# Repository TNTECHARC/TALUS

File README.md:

# TALUS GEN II
New repository for 2nd get TALUS (Raspberry Pi base).

## Centralized cloud for code, hardware, and cad models.

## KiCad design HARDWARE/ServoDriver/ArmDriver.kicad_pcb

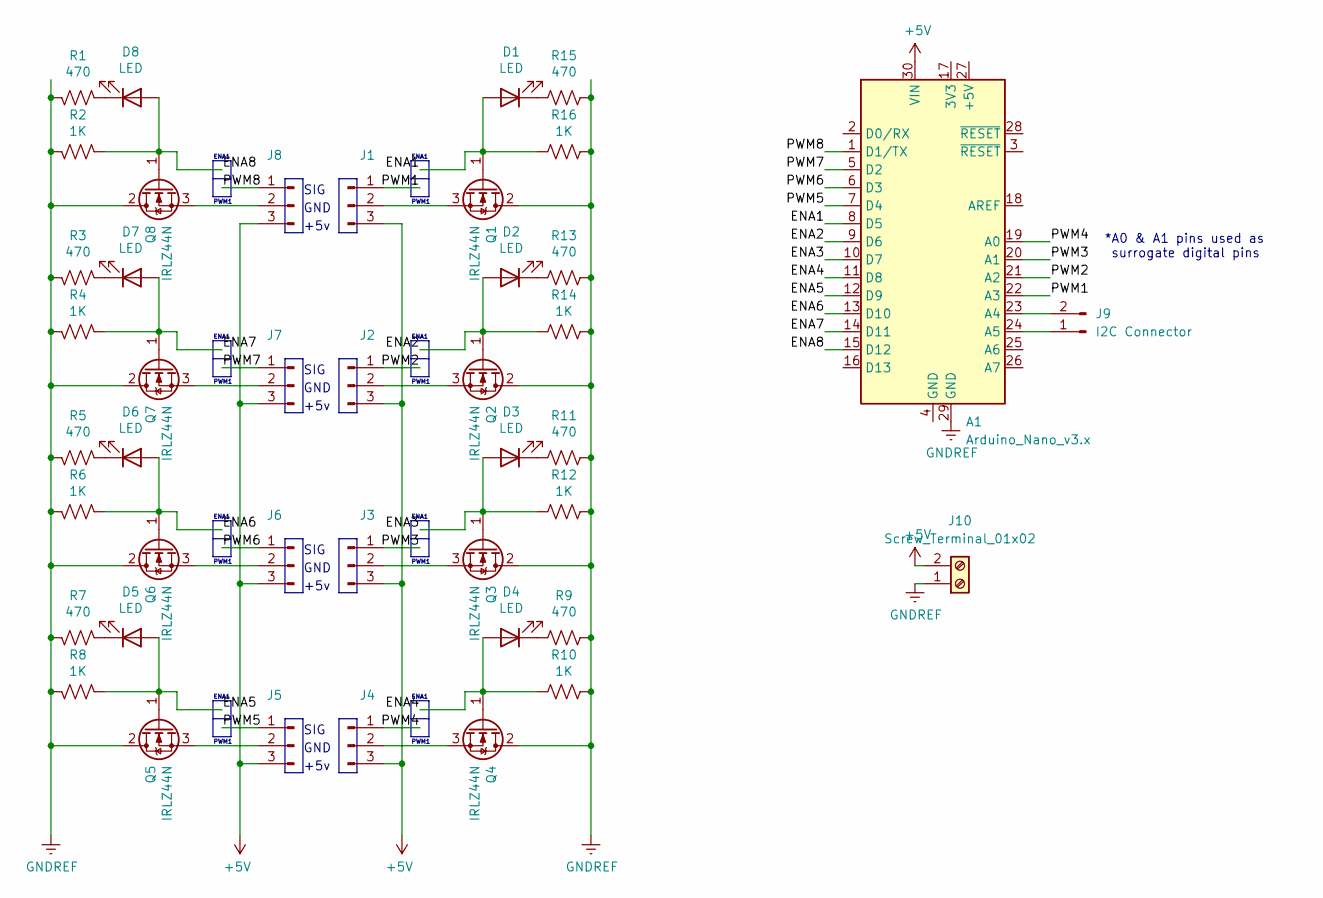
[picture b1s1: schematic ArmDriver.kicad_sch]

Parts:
A1: Arduino_Nano_v3.x; Arduino_Nano
D1, D2, D3, D4, D5, D6, D7, D8: LED; LED_D3.0mm
J1, J2, J3, J4, J5, J6, J7, J8: Conn_01x03_Male; PinHeader_1x03_P2.54mm_Vertical
J9: I2C Connector; PinHeader_1x02_P2.54mm_Vertical
J10: Screw_Terminal_01x02; TerminalBlock_Altech_AK300-2_P5.00mm
Q1, Q2, Q3, Q4, Q5, Q6, Q7, Q8: IRLZ44N; TO-218-3_Vertical
R1, R3, R5, R7, R9, R11, R13, R15: 470; R_Axial_DIN0204_L3.6mm_D1.6mm_P2.54mm_Vertical
R2, R4, R6, R8, R10, R12, R14, R16: 1K; R_Axial_DIN0204_L3.6mm_D1.6mm_P2.54mm_Vertical

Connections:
+5V: A1.30 (VIN), J1.3, J2.3, J3.3, J4.3, J5.3, J6.3, J7.3, J8.3, J10.2
/ENA1: A1.8 (D5), D1.2 (A), Q1.1 (G), R16.2
/ENA2: A1.9 (D6), D2.2 (A), Q2.1 (G), R14.2
/ENA3: A1.10 (D7), D3.2 (A), Q3.1 (G), R12.2
/ENA4: A1.11 (D8), D4.2 (A), Q4.1 (G), R10.2
/ENA5: A1.12 (D9), D5.2 (A), Q5.1 (G), R8.2
/ENA6: A1.13 (D10), D6.2 (A), Q6.1 (G), R6.2
/ENA7: A1.14 (D11), D7.2 (A), Q7.1 (G), R4.2
/ENA8: A1.15 (D12), D8.2 (A), Q8.1 (G), R2.2
/PWM1: A1.22 (A3), J1.1
/PWM2: A1.21 (A2), J2.1
/PWM3: A1.20 (A1), J3.1
/PWM4: A1.19 (A0), J4.1
/PWM5: A1.7 (D4), J5.1
/PWM6: A1.6 (D3), J6.1
/PWM7: A1.5 (D2), J7.1
/PWM8: A1.1 (D1/TX), J8.1
GNDREF: A1.29 (GND), J10.1, Q1.2 (D), Q2.2 (D), Q3.2 (D), Q4.2 (D), Q5.2 (D), Q6.2 (D), Q7.2 (D), Q8.2 (D), R1.1, R2.1, R3.1, R4.1, R5.1, R6.1, R7.1, R8.1, R9.1, R10.1, R11.1, R12.1, R13.1, R14.1, R15.1, R16.1; also elsewhere on the board
unnamed: A1.23 (A4), J9.2
unnamed: A1.24 (A5), J9.1
unnamed: D1.1 (K), R15.2
unnamed: D2.1 (K), R13.2
unnamed: D3.1 (K), R11.2
unnamed: D4.1 (K), R9.2
unnamed: D5.1 (K), R7.2
unnamed: D6.1 (K), R5.2
unnamed: D7.1 (K), R3.2
unnamed: D8.1 (K), R1.2
unnamed: J1.2, Q1.3 (S)
unnamed: J2.2, Q2.3 (S)
unnamed: J3.2, Q3.3 (S)
unnamed: J4.2, Q4.3 (S)
unnamed: J5.2, Q5.3 (S)
unnamed: J6.2, Q6.3 (S)
unnamed: J7.2, Q7.3 (S)
unnamed: J8.2, Q8.3 (S)
unnamed 36: A1.25 (A6); also elsewhere on the board

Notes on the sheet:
PWM1
SIG
ENA1
+5v
*A0 & A1 pins used as surrogate digital pins
GND

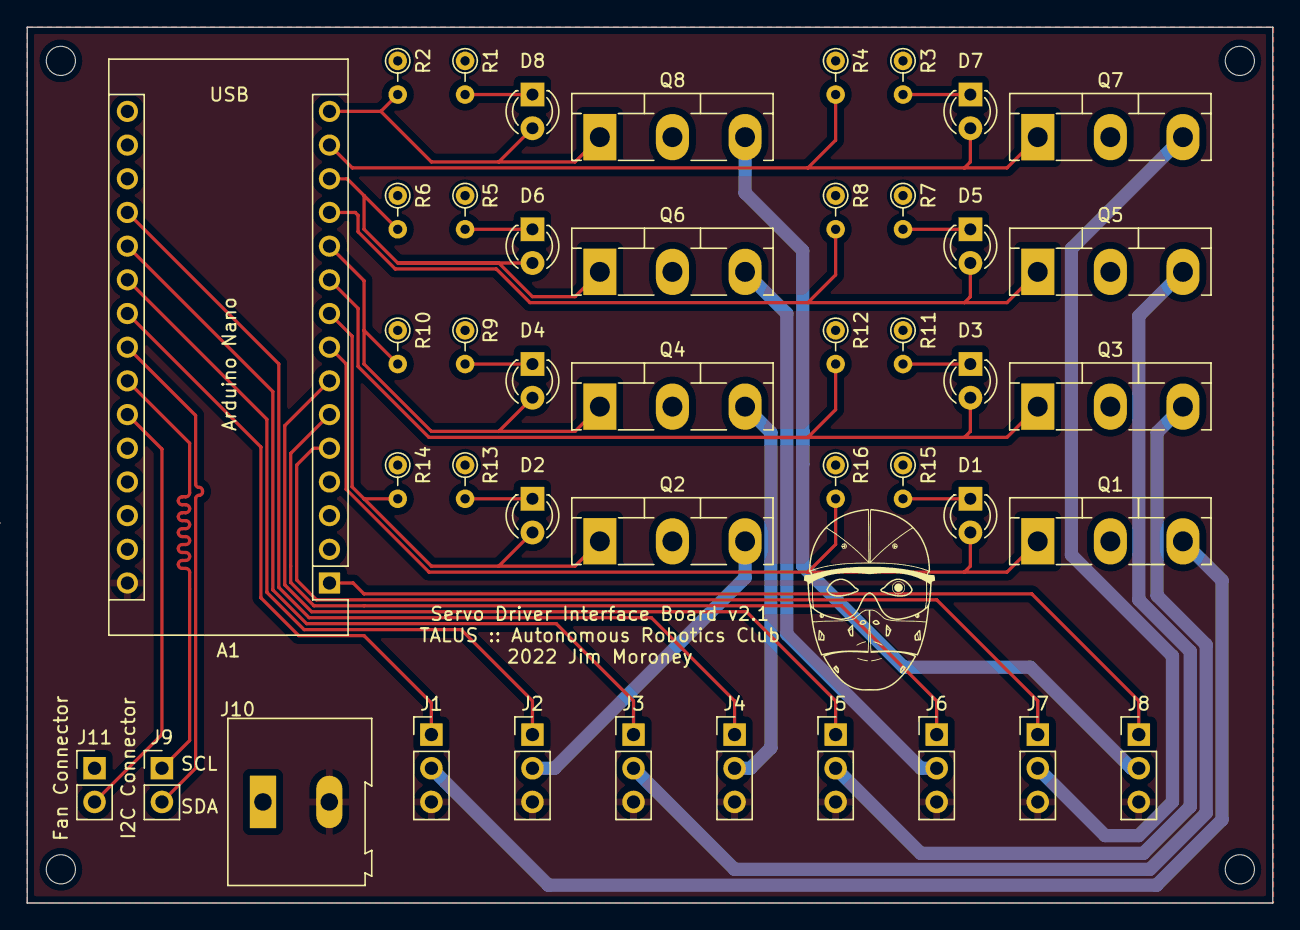
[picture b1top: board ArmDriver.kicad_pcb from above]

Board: 2 copper layers, 93.9 x 66.0 mm, 48 parts (0 on the bottom side), 37 nets.

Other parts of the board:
J11: Fan Connector; PinHeader_1x02_P2.54mm_Vertical
REF0, REF1, REF2, REF3: MountingHole_2.2mm_M2

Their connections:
GNDREF: J11.1; also elsewhere on the board
unnamed 36: J11.2; also elsewhere on the board

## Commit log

2022-02-27 ArmDriver rev2
2022-03-01 "Raspbian post-login file adeed"
